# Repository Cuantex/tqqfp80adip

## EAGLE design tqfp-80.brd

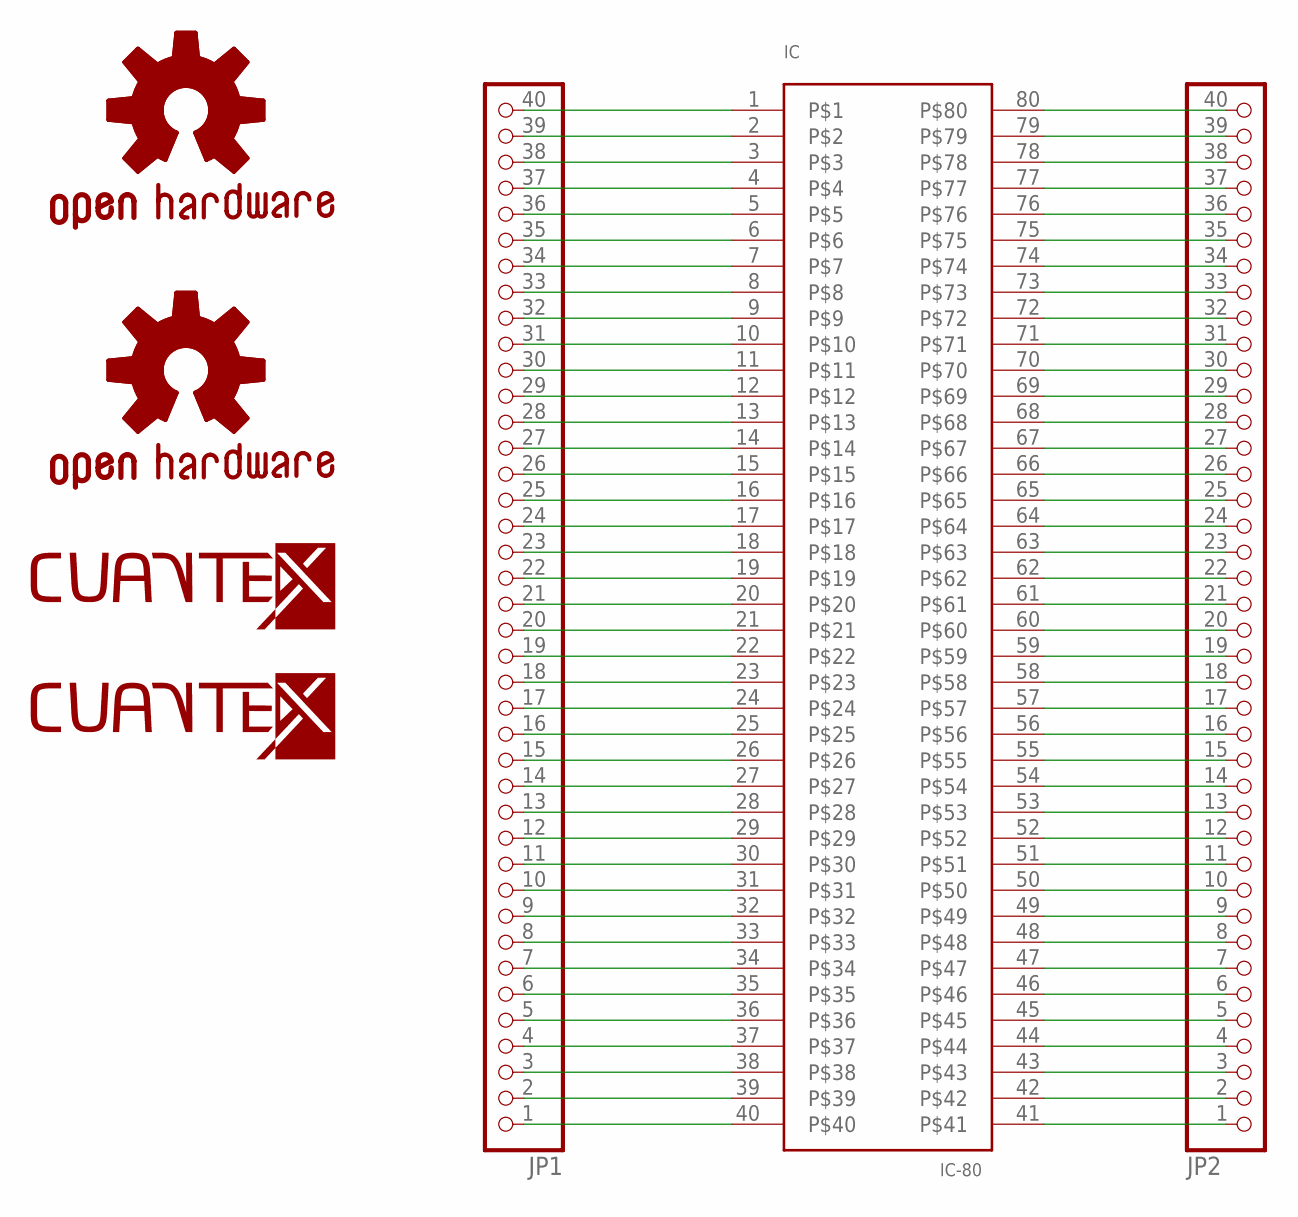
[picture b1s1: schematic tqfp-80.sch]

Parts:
GOLD_ORB_SM1, GOLD_ORB_SM2: OSHWLOGO_GOLD_ORB_SM; OSHW2
IC: IC-80; TQFP-80
JP1, JP2: PINHD-1X40; 1X40
U$2: LOGO-TOP-30MM; C-1
U$3: LOGO-TOP-15MM; C-00

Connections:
unnamed: IC.40, JP1.1
unnamed: IC.39, JP1.2
unnamed: IC.38, JP1.3
unnamed: IC.37, JP1.4
unnamed: IC.36, JP1.5
unnamed: IC.35, JP1.6
unnamed: IC.34, JP1.7
unnamed: IC.33, JP1.8
unnamed: IC.32, JP1.9
unnamed: IC.31, JP1.10
unnamed: IC.30, JP1.11
unnamed: IC.29, JP1.12
unnamed: IC.28, JP1.13
unnamed: IC.27, JP1.14
unnamed: IC.26, JP1.15
unnamed: IC.25, JP1.16
unnamed: IC.24, JP1.17
unnamed: IC.23, JP1.18
unnamed: IC.22, JP1.19
unnamed: IC.21, JP1.20
unnamed: IC.20, JP1.21
unnamed: IC.19, JP1.22
unnamed: IC.18, JP1.23
unnamed: IC.17, JP1.24
unnamed: IC.16, JP1.25
unnamed: IC.15, JP1.26
unnamed: IC.14, JP1.27
unnamed: IC.13, JP1.28
unnamed: IC.12, JP1.29
unnamed: IC.11, JP1.30
unnamed: IC.10, JP1.31
unnamed: IC.9, JP1.32
unnamed: IC.8, JP1.33
unnamed: IC.7, JP1.34
unnamed: IC.6, JP1.35
unnamed: IC.5, JP1.36
unnamed: IC.4, JP1.37
unnamed: IC.3, JP1.38
unnamed: IC.2, JP1.39
unnamed: IC.1, JP1.40
unnamed: IC.41, JP2.1
unnamed: IC.42, JP2.2
unnamed: IC.43, JP2.3
unnamed: IC.44, JP2.4
unnamed: IC.45, JP2.5
unnamed: IC.46, JP2.6
unnamed: IC.47, JP2.7
unnamed: IC.48, JP2.8
unnamed: IC.49, JP2.9
unnamed: IC.50, JP2.10
unnamed: IC.51, JP2.11
unnamed: IC.52, JP2.12
unnamed: IC.53, JP2.13
unnamed: IC.54, JP2.14
unnamed: IC.55, JP2.15
unnamed: IC.56, JP2.16
unnamed: IC.57, JP2.17
unnamed: IC.58, JP2.18
unnamed: IC.59, JP2.19
unnamed: IC.60, JP2.20
unnamed: IC.61, JP2.21
unnamed: IC.62, JP2.22
unnamed: IC.63, JP2.23
unnamed: IC.64, JP2.24
unnamed: IC.65, JP2.25
unnamed: IC.66, JP2.26
unnamed: IC.67, JP2.27
unnamed: IC.68, JP2.28
unnamed: IC.69, JP2.29
unnamed: IC.70, JP2.30
unnamed: IC.71, JP2.31
unnamed: IC.72, JP2.32
unnamed: IC.73, JP2.33
unnamed: IC.74, JP2.34
unnamed: IC.75, JP2.35
unnamed: IC.76, JP2.36
unnamed: IC.77, JP2.37
unnamed: IC.78, JP2.38
unnamed: IC.79, JP2.39
unnamed: IC.80, JP2.40

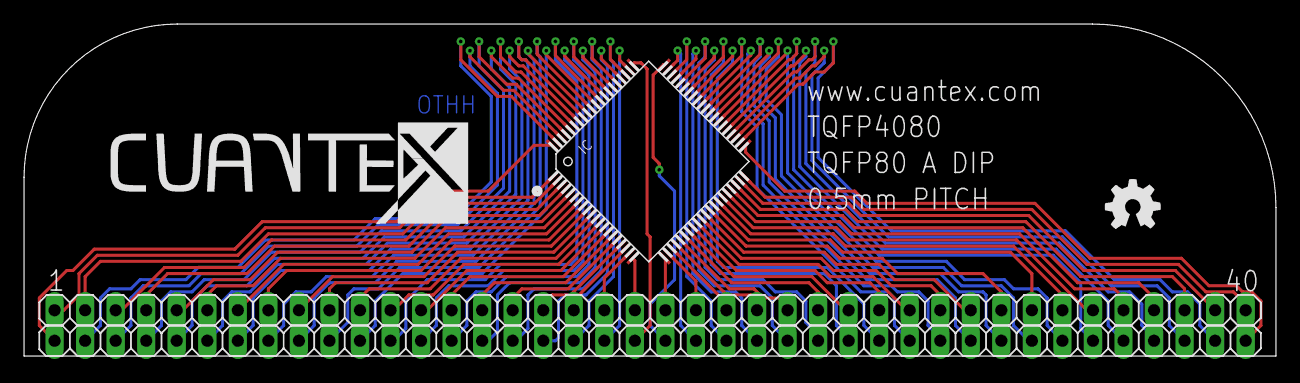
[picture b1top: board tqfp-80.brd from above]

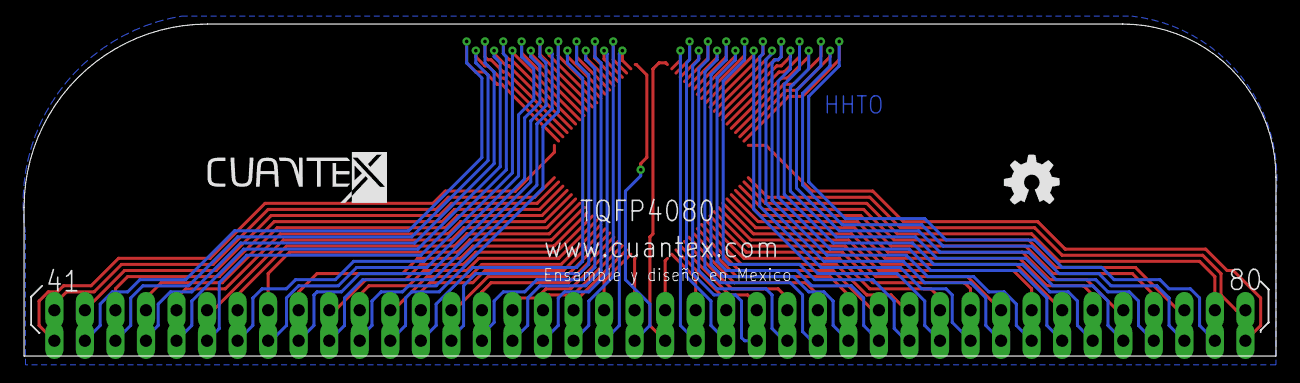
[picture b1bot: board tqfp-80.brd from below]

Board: 2 copper layers, 104.1 x 27.6 mm, 7 parts (2 on the bottom side), 80 nets.

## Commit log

2016-10-13 Archivos en Git
